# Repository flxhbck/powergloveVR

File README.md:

# PowergloveVR

Resources to modify the Powerglove to become compatible with the HTC Vive VR system. Requires a Vive tracker puck and an Arduino Due. 

This project was done at Teague Labs.

## Arduino
This code is written for the Arduino Due! The program reads the analog values of the bending sensors and communicates to the HTC Vive Tracker. The code performs “auto-calibration” on the sensor values and smoothes the values over time. The communication between the Arduino Due and the Vive tracker builds on the USB-Host Library extension by [matzmann666](https://github.com/matzman666/USBHost). Since only three analog values can be transmitted via the tracker, the middle and ring finger values are alternated over time.

## CAD
Printable and editable files for mounting the Vive tracker and Arduino Due on the Powerglove.

## Eagle
Arduino Due Shield for reading the analog bending sensors of the Powerglove. Includes battery charging module, two indicator LEDs, and a push-button. The folder also includes the image-file we used for etching.
This is a very quick and dirty design, so use it cautiously. When you look at the board design, you’ll see that some extra bridge-wires have to be soldered to the pads. The board works, but there are couple of missteps. Most importantly, the charger footprint is off.

## Unity
Example project with a rigged hand model that listens to the puck.

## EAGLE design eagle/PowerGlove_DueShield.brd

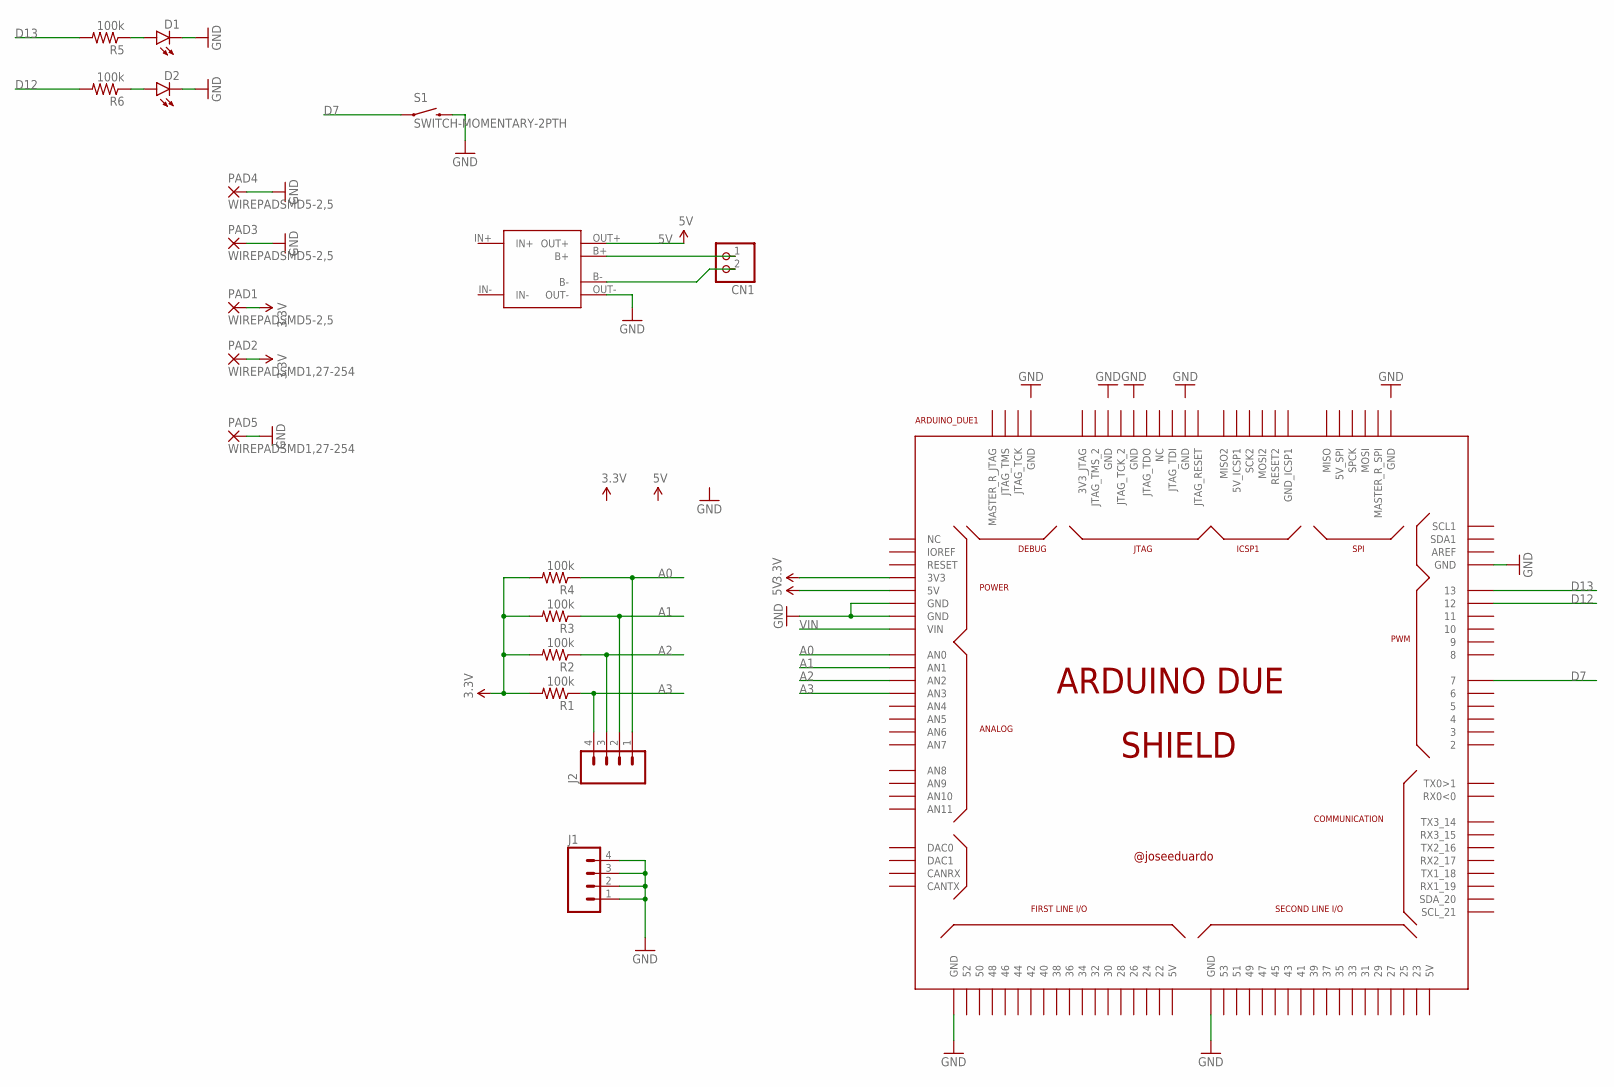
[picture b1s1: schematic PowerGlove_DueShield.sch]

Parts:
ARDUINO_DUE1: ARDUINO_DUE_SHIELD
CN1: JST_2PIN-THM-RA; JST-PH-2-THM-RA
D1, D2: LED3MM
J1, J2: M04LONGPADS; 1X04_LONGPADS
PAD1, PAD3, PAD4: WIREPADSMD5-2,5; 5-2,5
PAD2, PAD5: WIREPADSMD1,27-254; SMD1,27-2,54
R1, R2, R3, R4, R5, R6: 100k; 0207/10
S1: SWITCH-MOMENTARY-2PTH; TACTILE-PTH
U$1: TP4056-MODULE; TP4056-LITHIUM-PROTECTED-MODULE

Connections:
3.3V: ARDUINO_DUE1.3V3, PAD1.1, PAD2.1, R1.2, R2.2, R3.2, R4.2
5V: ARDUINO_DUE1.5V0 (5V), U$1.OUT+
A0: ARDUINO_DUE1.A0 (AN0), J2.1, R4.1
A1: ARDUINO_DUE1.A1 (AN1), J2.2, R3.1
A2: ARDUINO_DUE1.A2 (AN2), J2.3, R2.1
A3: ARDUINO_DUE1.A3 (AN3), J2.4, R1.1
B+: CN1.1 (2), U$1.B+
B-: CN1.2 (1), U$1.B-
D7: ARDUINO_DUE1.7, S1.1
D12: ARDUINO_DUE1.12, R6.2
D13: ARDUINO_DUE1.13, R5.2
GND: ARDUINO_DUE1.GND, ARDUINO_DUE1.GND_1 (GND), ARDUINO_DUE1.GND_2 (GND), ARDUINO_DUE1.GND_3 (GND), ARDUINO_DUE1.GND_4 (GND), D1.K (C), D2.K (C), J1.1, J1.2, J1.3, J1.4, PAD3.1, PAD4.1, PAD5.1, S1.3 (2), U$1.OUT-
IN+: U$1.IN+
IN-: U$1.IN-
unnamed: D1.A, R5.1
unnamed: D2.A, R6.1
VIN: ARDUINO_DUE1.VIN

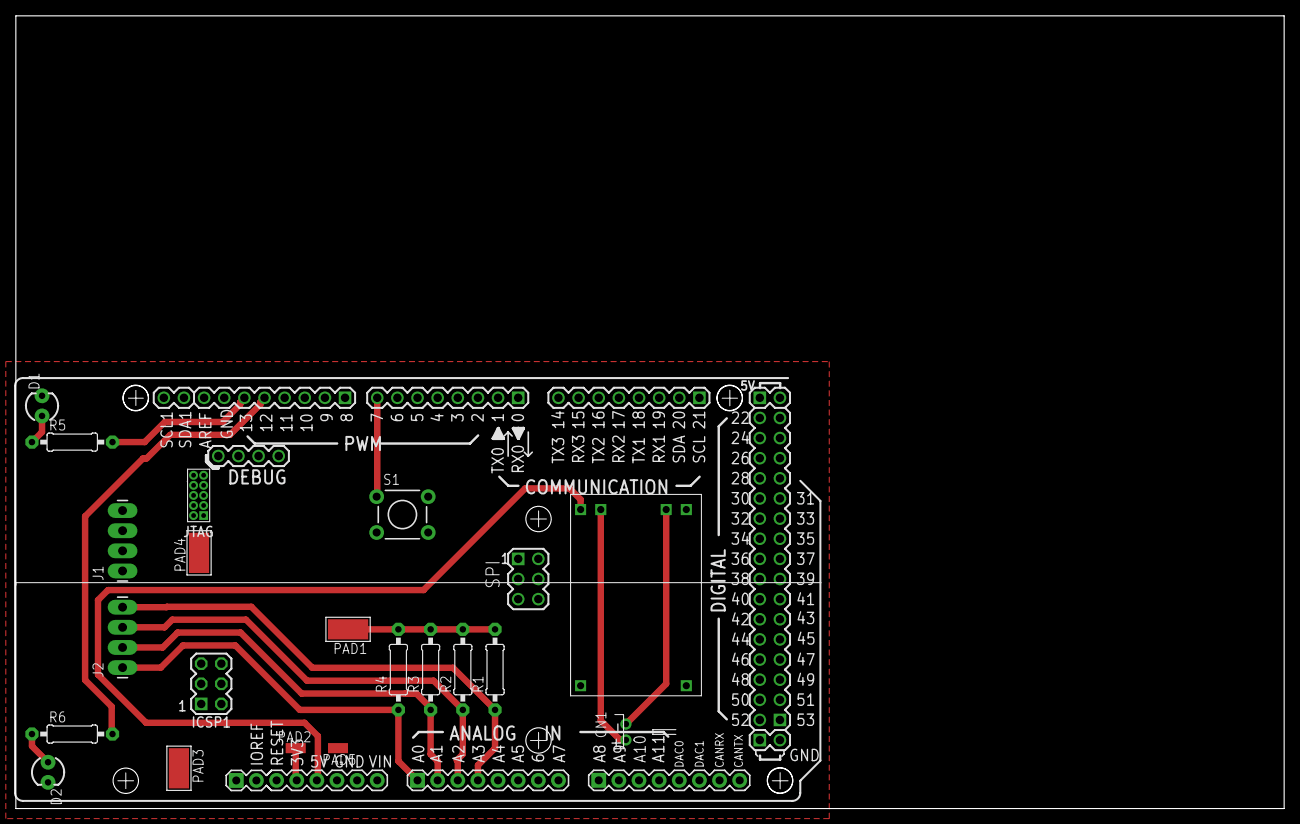
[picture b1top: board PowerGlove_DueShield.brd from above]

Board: 2 copper layers, 160.0 x 100.0 mm, 19 parts (0 on the bottom side), 14 nets.

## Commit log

2017-08-24 add eagle and arduino files.
2017-08-24 readme.
2017-08-24 add CAD files

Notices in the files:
parts and their libraries:
SparkFun-Connectors: Licensing: Creative Commons ShareAlike 4.0 International - https://creativecommons.org/licenses/by-sa/4.0
